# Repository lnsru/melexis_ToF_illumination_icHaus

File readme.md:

# Illumination board

This board to be used with time of flight camera. There are interesting chips from Melexis, Infineon, TI and Sony. [My another repository](https://github.com/lnsru/melexis_VGA_ToF_camera "VGA time of flight camera") contains design with Melexis VGA resolution time of flight sensor.

[Higly integrated chip from iC-Haus](http://www.ichaus.de/product/iC-HGP "iC-HGP") was choosen for simpler design. It is specialized high current high speed swich for applications like this one. Buy some from [iC-Haus USA shop.](https://us-shop.ichaus.com/ProductDetails.asp?ProductCode=iC%2DHGP "Buy iC-HGP") 

The design should work with LEDs from Osram and Lumileds. Check datasheet for needed exact voltage, I assume, it will work with 10-12 V power supply.

Following parts are supported:
* Lumileds L1IG-0850000000000 (assembled on prototype board)
* Lumileds L1IG-0940000000000
* Osram SFH 4770S
* Osram SFH 4775S

Note: modern phones have infrared filters and can't take nice photos. The glowing red is LED illumination in visible spectrum. The pulses were seen with iPhone 3G and oscilloscope.

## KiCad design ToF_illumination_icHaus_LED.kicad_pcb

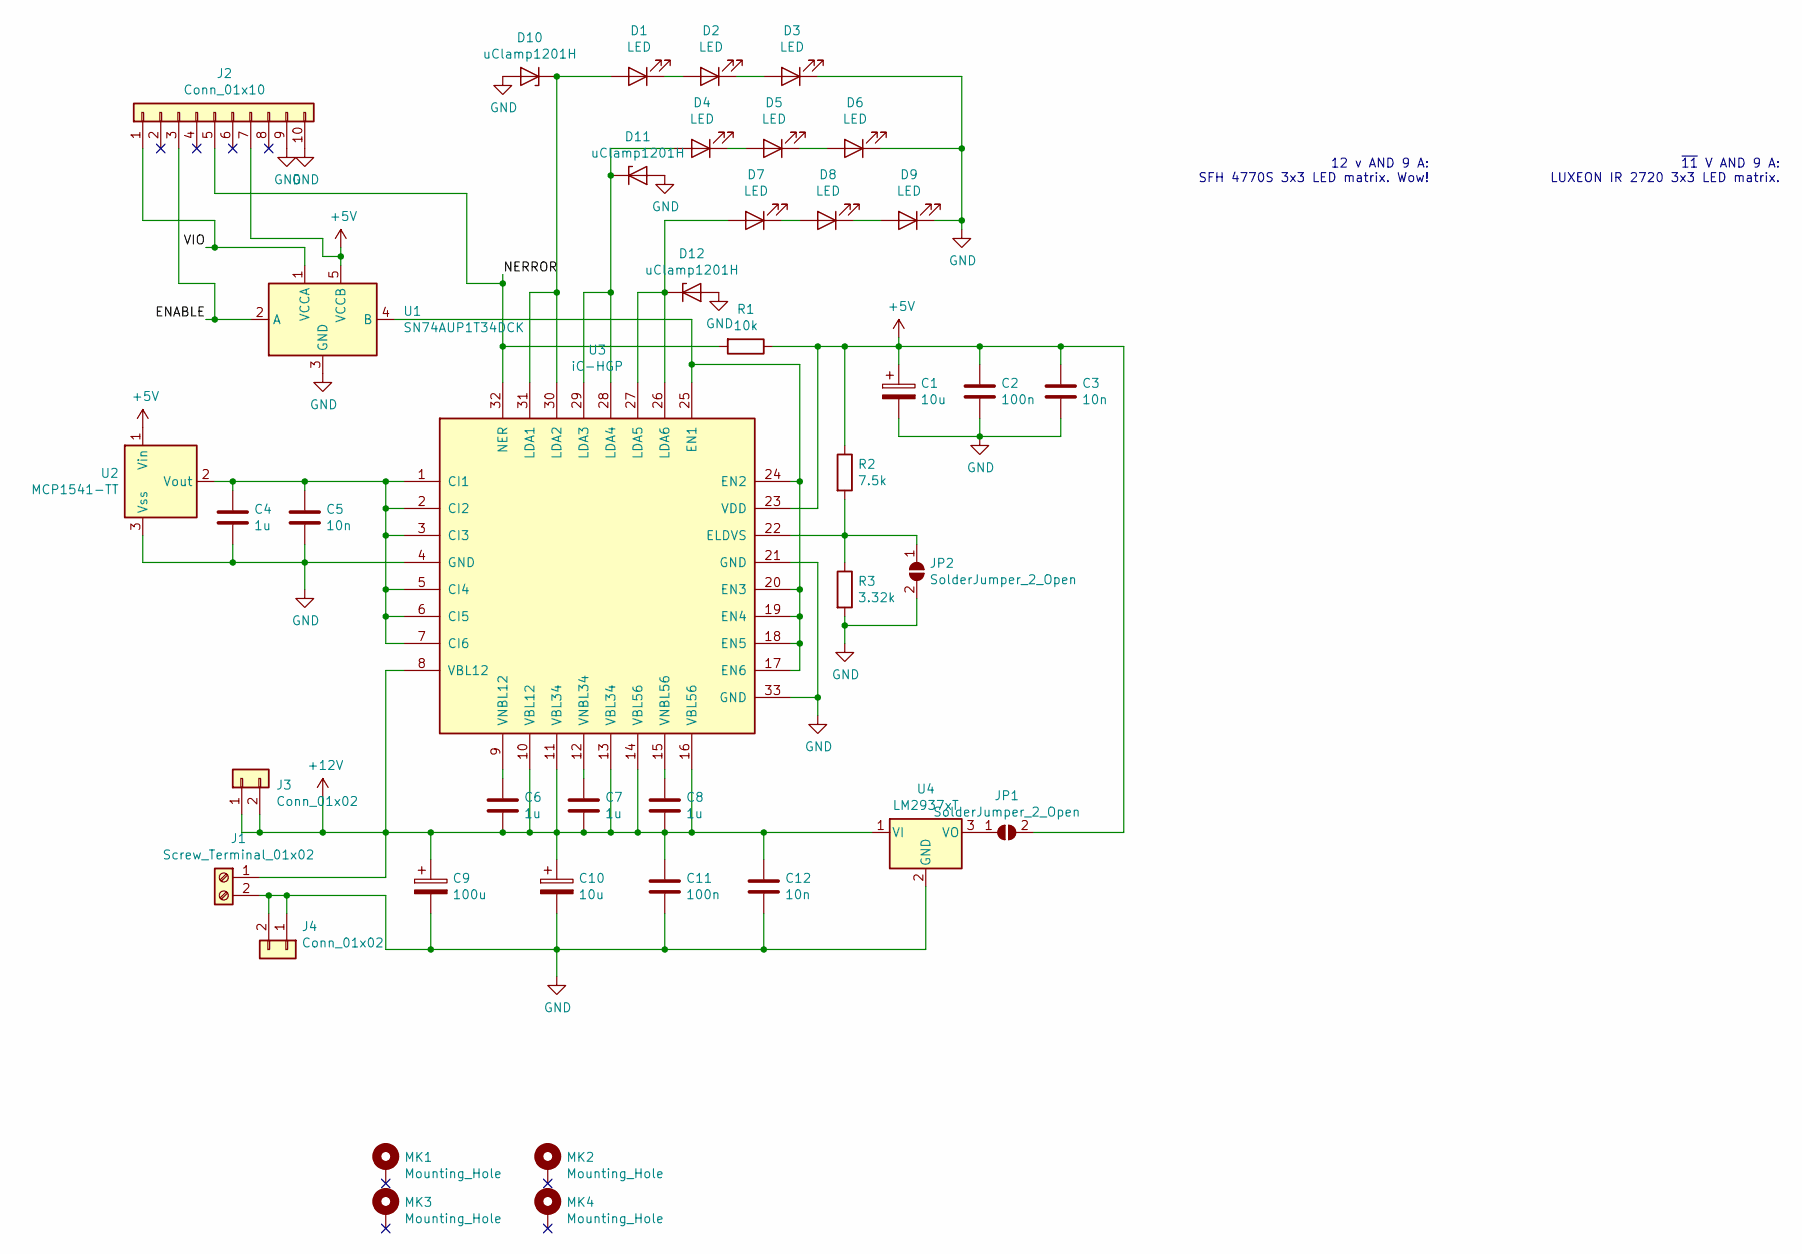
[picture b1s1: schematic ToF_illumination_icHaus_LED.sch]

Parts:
C1, C10: 10u; C_1210
C2, C11: 100n; C_0805
C3, C5, C12: 10n; C_0805
C4, C6, C7, C8: 1u; C_0805
C9: 100u; C_1210
D1, D2, D3, D4, D5, D6, D7, D8, D9: LED; LuxeonIR2720_singlePad
D10, D11, D12: uClamp1201H; D_SOD-523
J1: Screw_Terminal_01x02; TerminalBlock_bornier-2_P5.08mm
J2: Conn_01x10; Pin_Header_Straight_1x10_Pitch2.54mm
J3, J4: Conn_01x02; Pin_Header_Straight_1x02_Pitch2.54mm
JP1, JP2: SolderJumper_2_Open; GS2
MK1, MK2, MK3, MK4: Mounting_Hole; MountingHole_3.2mm_M3_ISO7380
R1: 10k; R_0805
R2: 7.5k; R_0805
R3: 3.32k; R_0805
U1: SN74AUP1T34DCK; SOT-353_SC-70-5
U2: MCP1541-TT; SOT-23
U3: iC-HGP; QFN_32_5x5mm_0.5mm_thermal
U4: LM2937xT; SOT-223

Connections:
+5V: C1.1, C2.1, C3.1, J2.7, JP1.2 (B), R1.1, R2.1, U1.5 (VCCB), U2.1 (Vin), U3.23 (VDD)
+12V: C6.1, C7.1, C8.1, C9.1, C10.1, C11.1, C12.1, J1.1, J3.1, J3.2, U3.8 (VBL12), U3.10 (VBL12), U3.11 (VBL34), U3.13 (VBL34), U3.14 (VBL56), U3.16 (VBL56), U4.1 (VI)
/ENABLE: J2.3, U1.2 (A)
/NERROR: J2.5, R1.2, U3.32 (NER)
/VIO: J2.1, U1.1 (VCCA)
GND: C1.2, C2.2, C3.2, C4.2, C5.2, C9.2, C10.2, C11.2, C12.2, D3.1 (K), D6.1 (K), D9.1 (K), D10.2 (A), D11.2 (A), D12.2 (A), J1.2, J2.9, J2.10, J4.1, J4.2, JP2.2 (B), R3.2, U1.3 (GND), U2.3 (Vss), U3.4 (GND), U3.21 (GND), U3.33 (GND), U4.2 (GND)
unnamed: C4.1, C5.1, U2.2 (Vout), U3.1 (CI1), U3.2 (CI2), U3.3 (CI3), U3.5 (CI4), U3.6 (CI5), U3.7 (CI6)
unnamed: C6.2, U3.9 (VNBL12)
unnamed: C7.2, U3.12 (VNBL34)
unnamed: C8.2, U3.15 (VNBL56)
unnamed: D1.1 (K), D2.2 (A)
unnamed: D1.2 (A), D10.1 (K), U3.30 (LDA2), U3.31 (LDA1)
unnamed: D2.1 (K), D3.2 (A)
unnamed: D4.1 (K), D5.2 (A)
unnamed: D5.1 (K), D6.2 (A)
unnamed: D7.1 (K), D8.2 (A)
unnamed: D8.1 (K), D9.2 (A)
unnamed: D4.2 (A), D11.1 (K), U3.28 (LDA4), U3.29 (LDA3)
unnamed: D7.2 (A), D12.1 (K), U3.26 (LDA6), U3.27 (LDA5)
unnamed: JP1.1 (A), U4.3 (VO)
unnamed: JP2.1 (A), R2.2, R3.1, U3.22 (ELDVS)
unnamed: U1.4 (B), U3.17 (EN6), U3.18 (EN5), U3.19 (EN4), U3.20 (EN3), U3.24 (EN2), U3.25 (EN1)

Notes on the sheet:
12 v AND 9 A: SFH 4770S 3x3 LED matrix. Wow!
~11 V AND 9 A: LUXEON IR 2720 3x3 LED matrix.

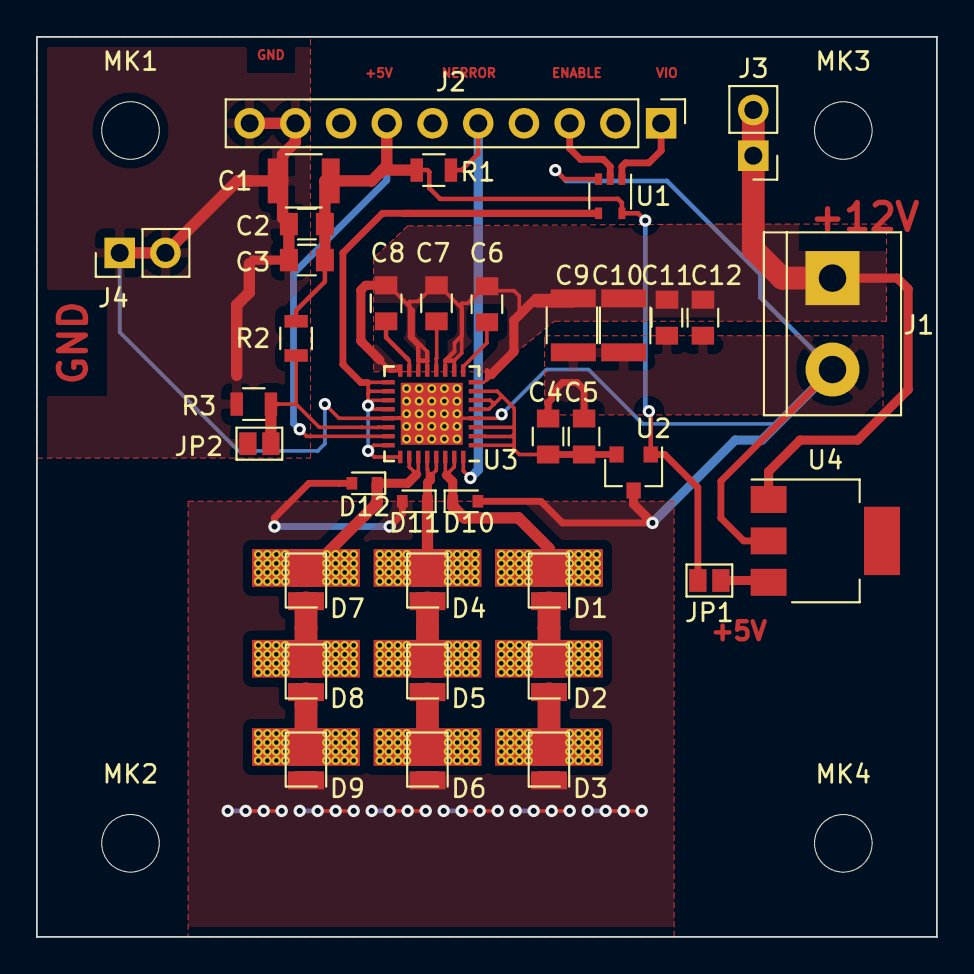
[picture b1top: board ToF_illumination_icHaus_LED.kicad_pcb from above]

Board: 2 copper layers, 50.0 x 50.0 mm, 41 parts (0 on the bottom side), 22 nets.

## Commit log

2019-08-20 Tantalum capacitors were changed to 1210 size and project was moved to KiCad 5.1.4
2019-08-20 Added BOM, improved footprints a bit.
2019-08-21 Updated BOM
2019-08-25 Gerbers added and some labels on the board for assembly added
2019-09-22 Looks like, this design is working!
2019-09-23 Photo added
2019-09-23 Beautifying readme file
